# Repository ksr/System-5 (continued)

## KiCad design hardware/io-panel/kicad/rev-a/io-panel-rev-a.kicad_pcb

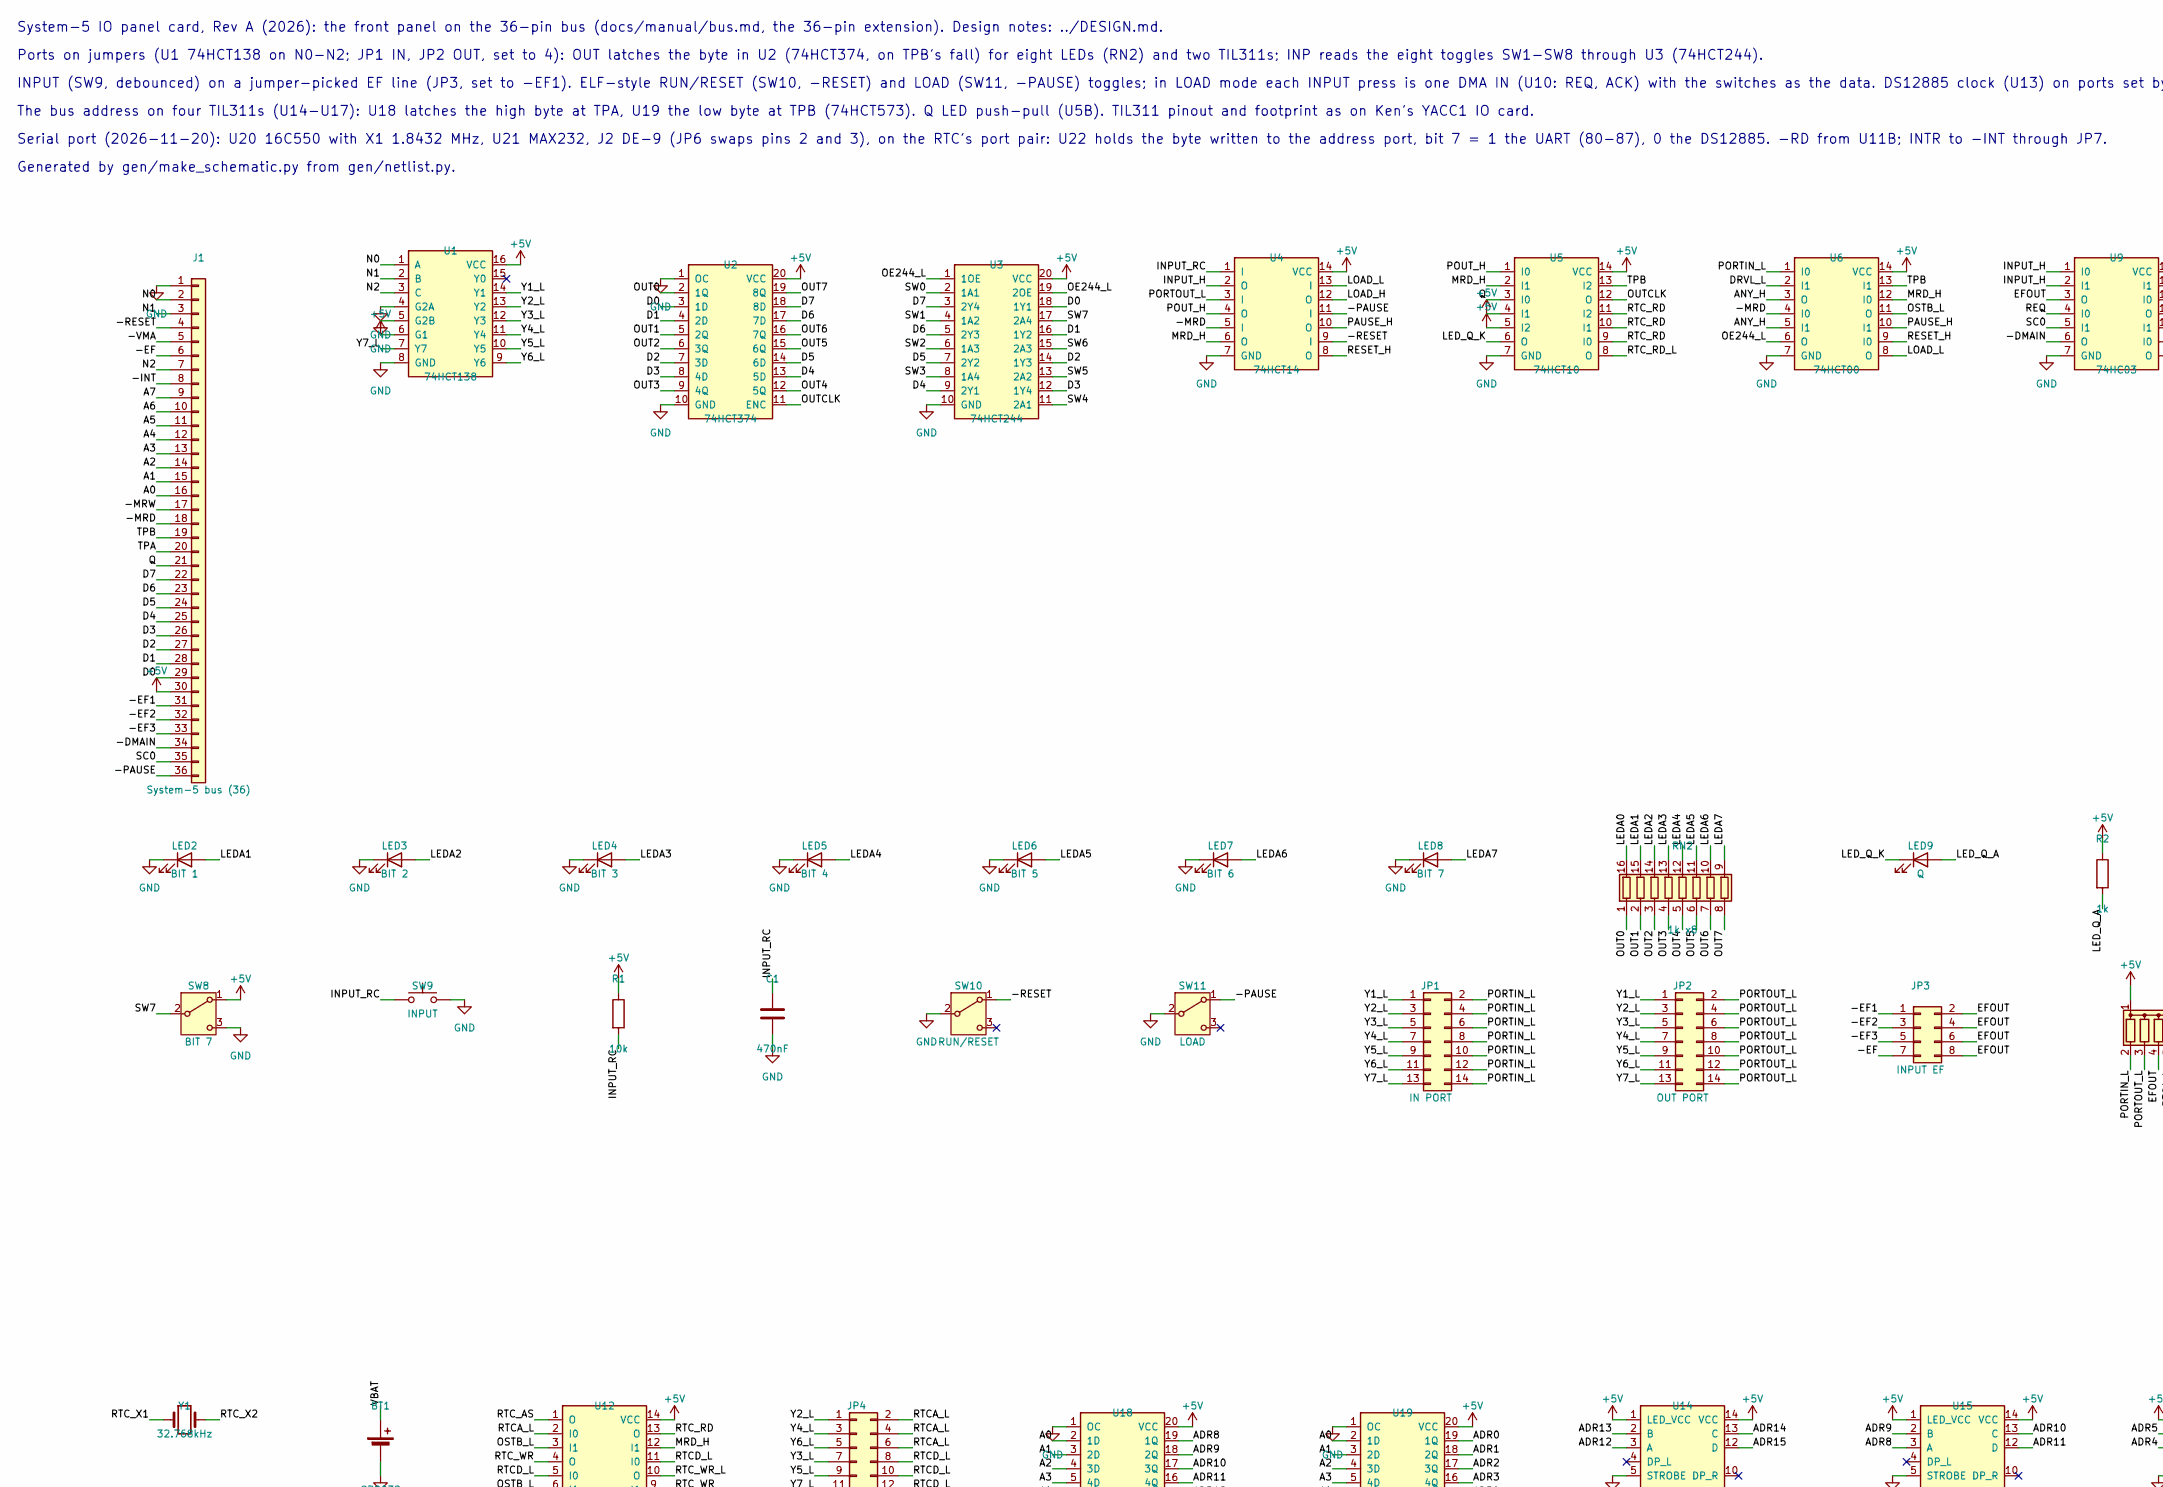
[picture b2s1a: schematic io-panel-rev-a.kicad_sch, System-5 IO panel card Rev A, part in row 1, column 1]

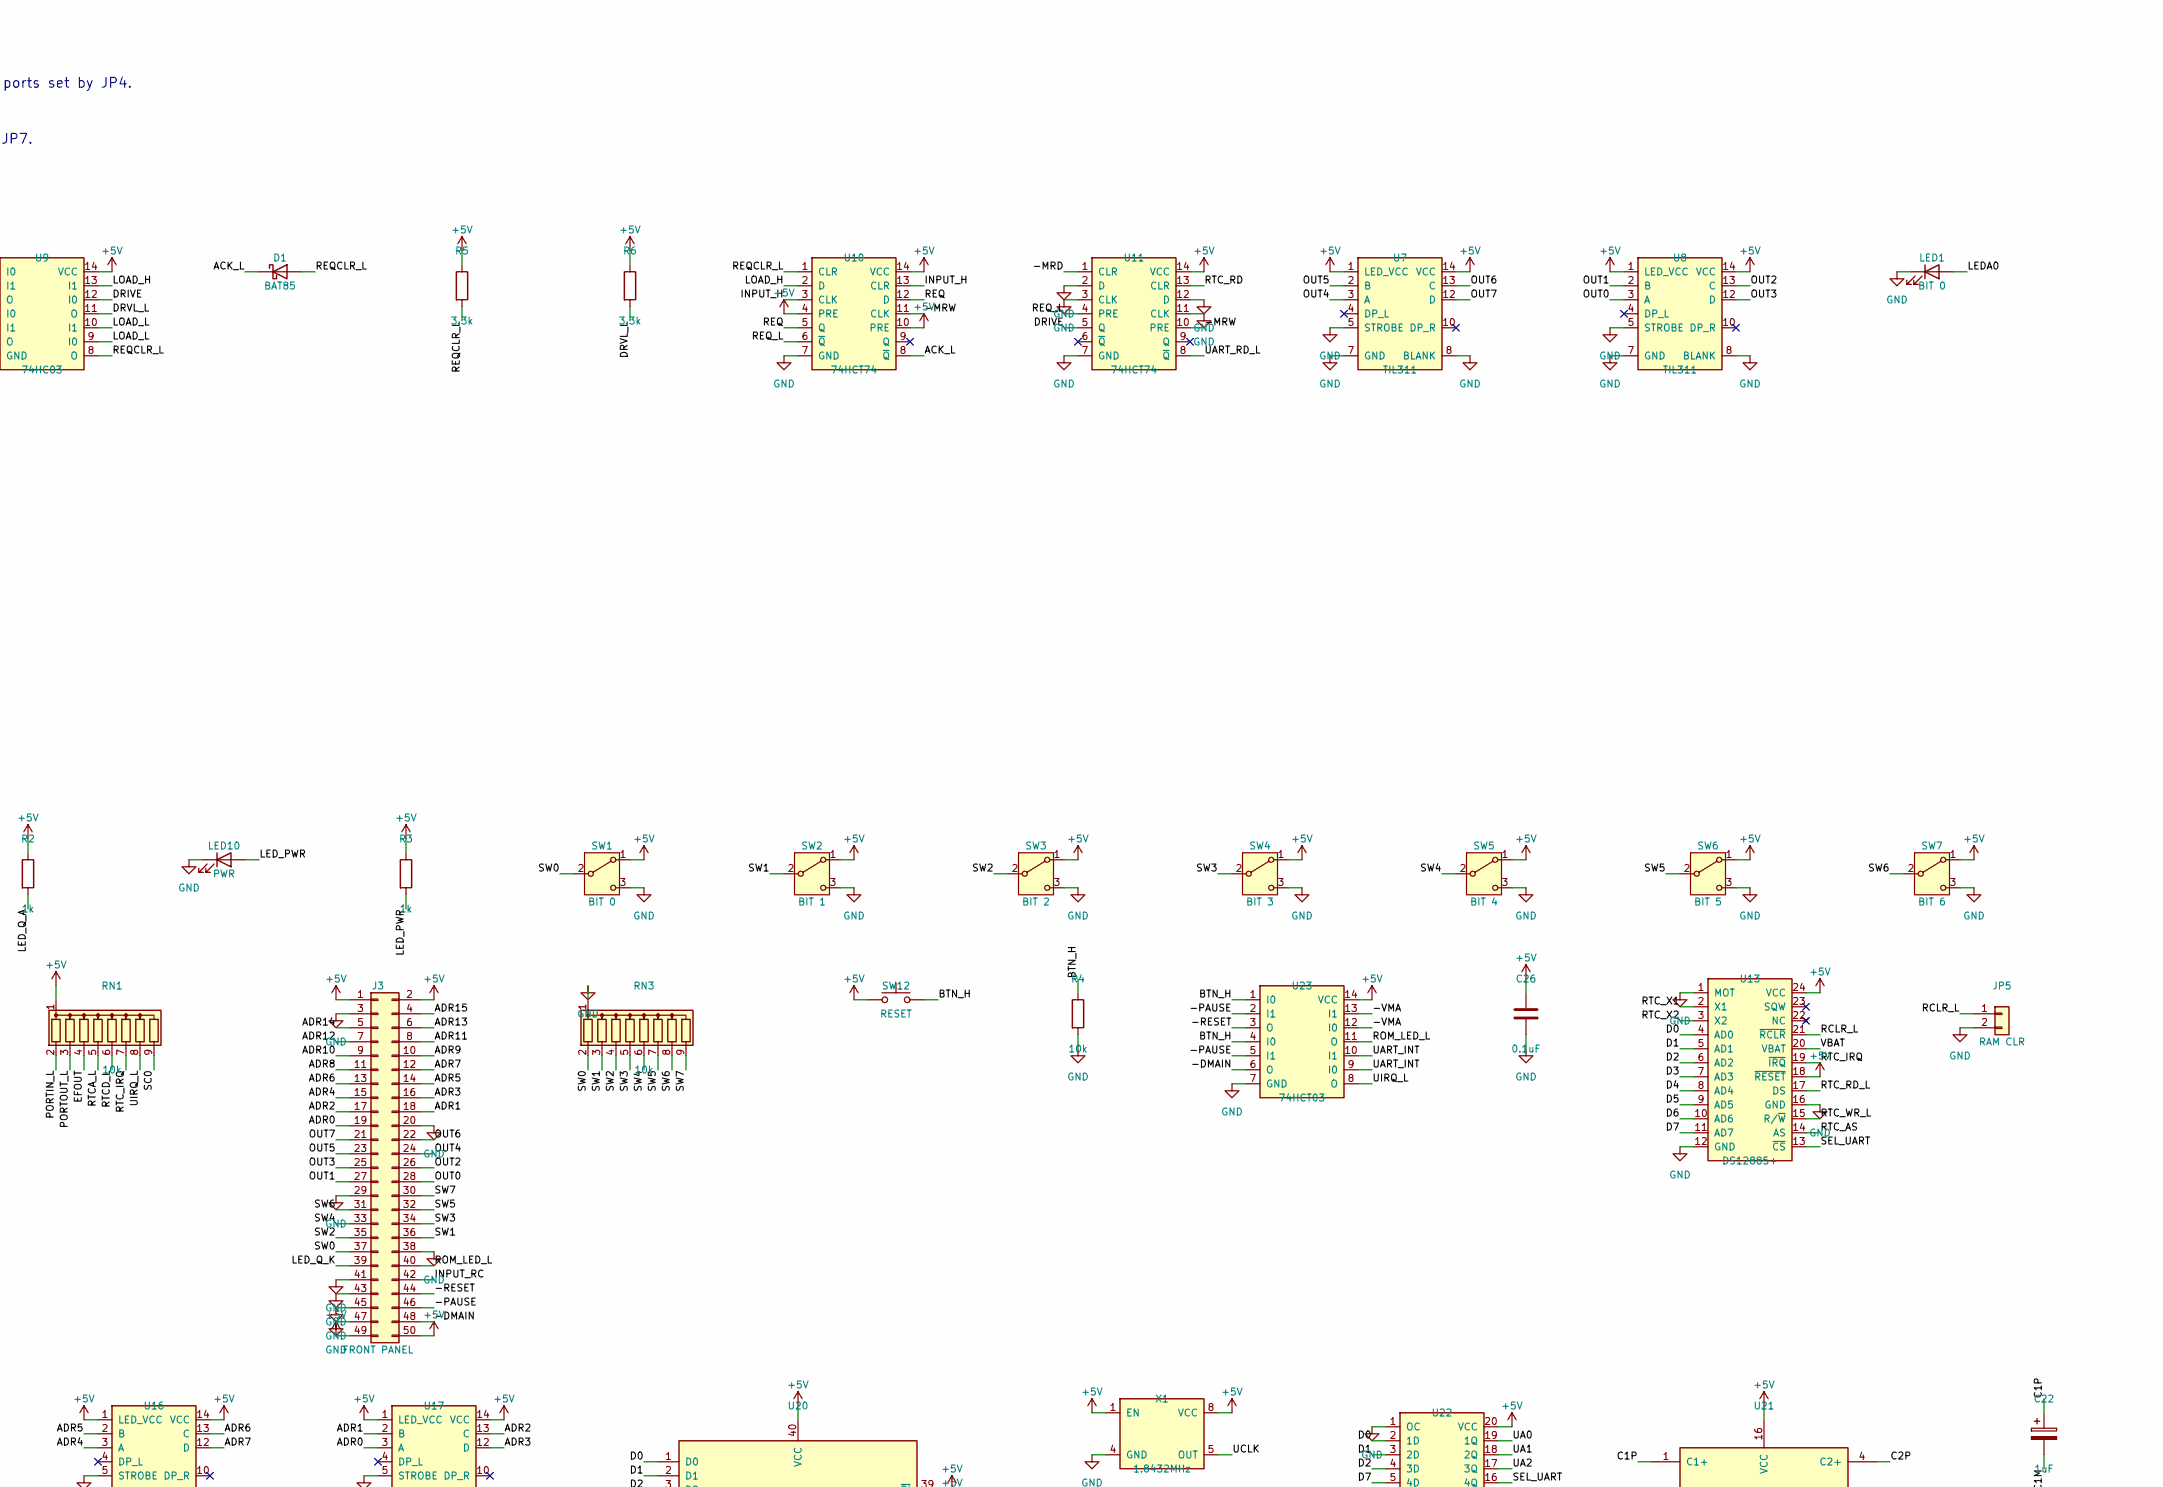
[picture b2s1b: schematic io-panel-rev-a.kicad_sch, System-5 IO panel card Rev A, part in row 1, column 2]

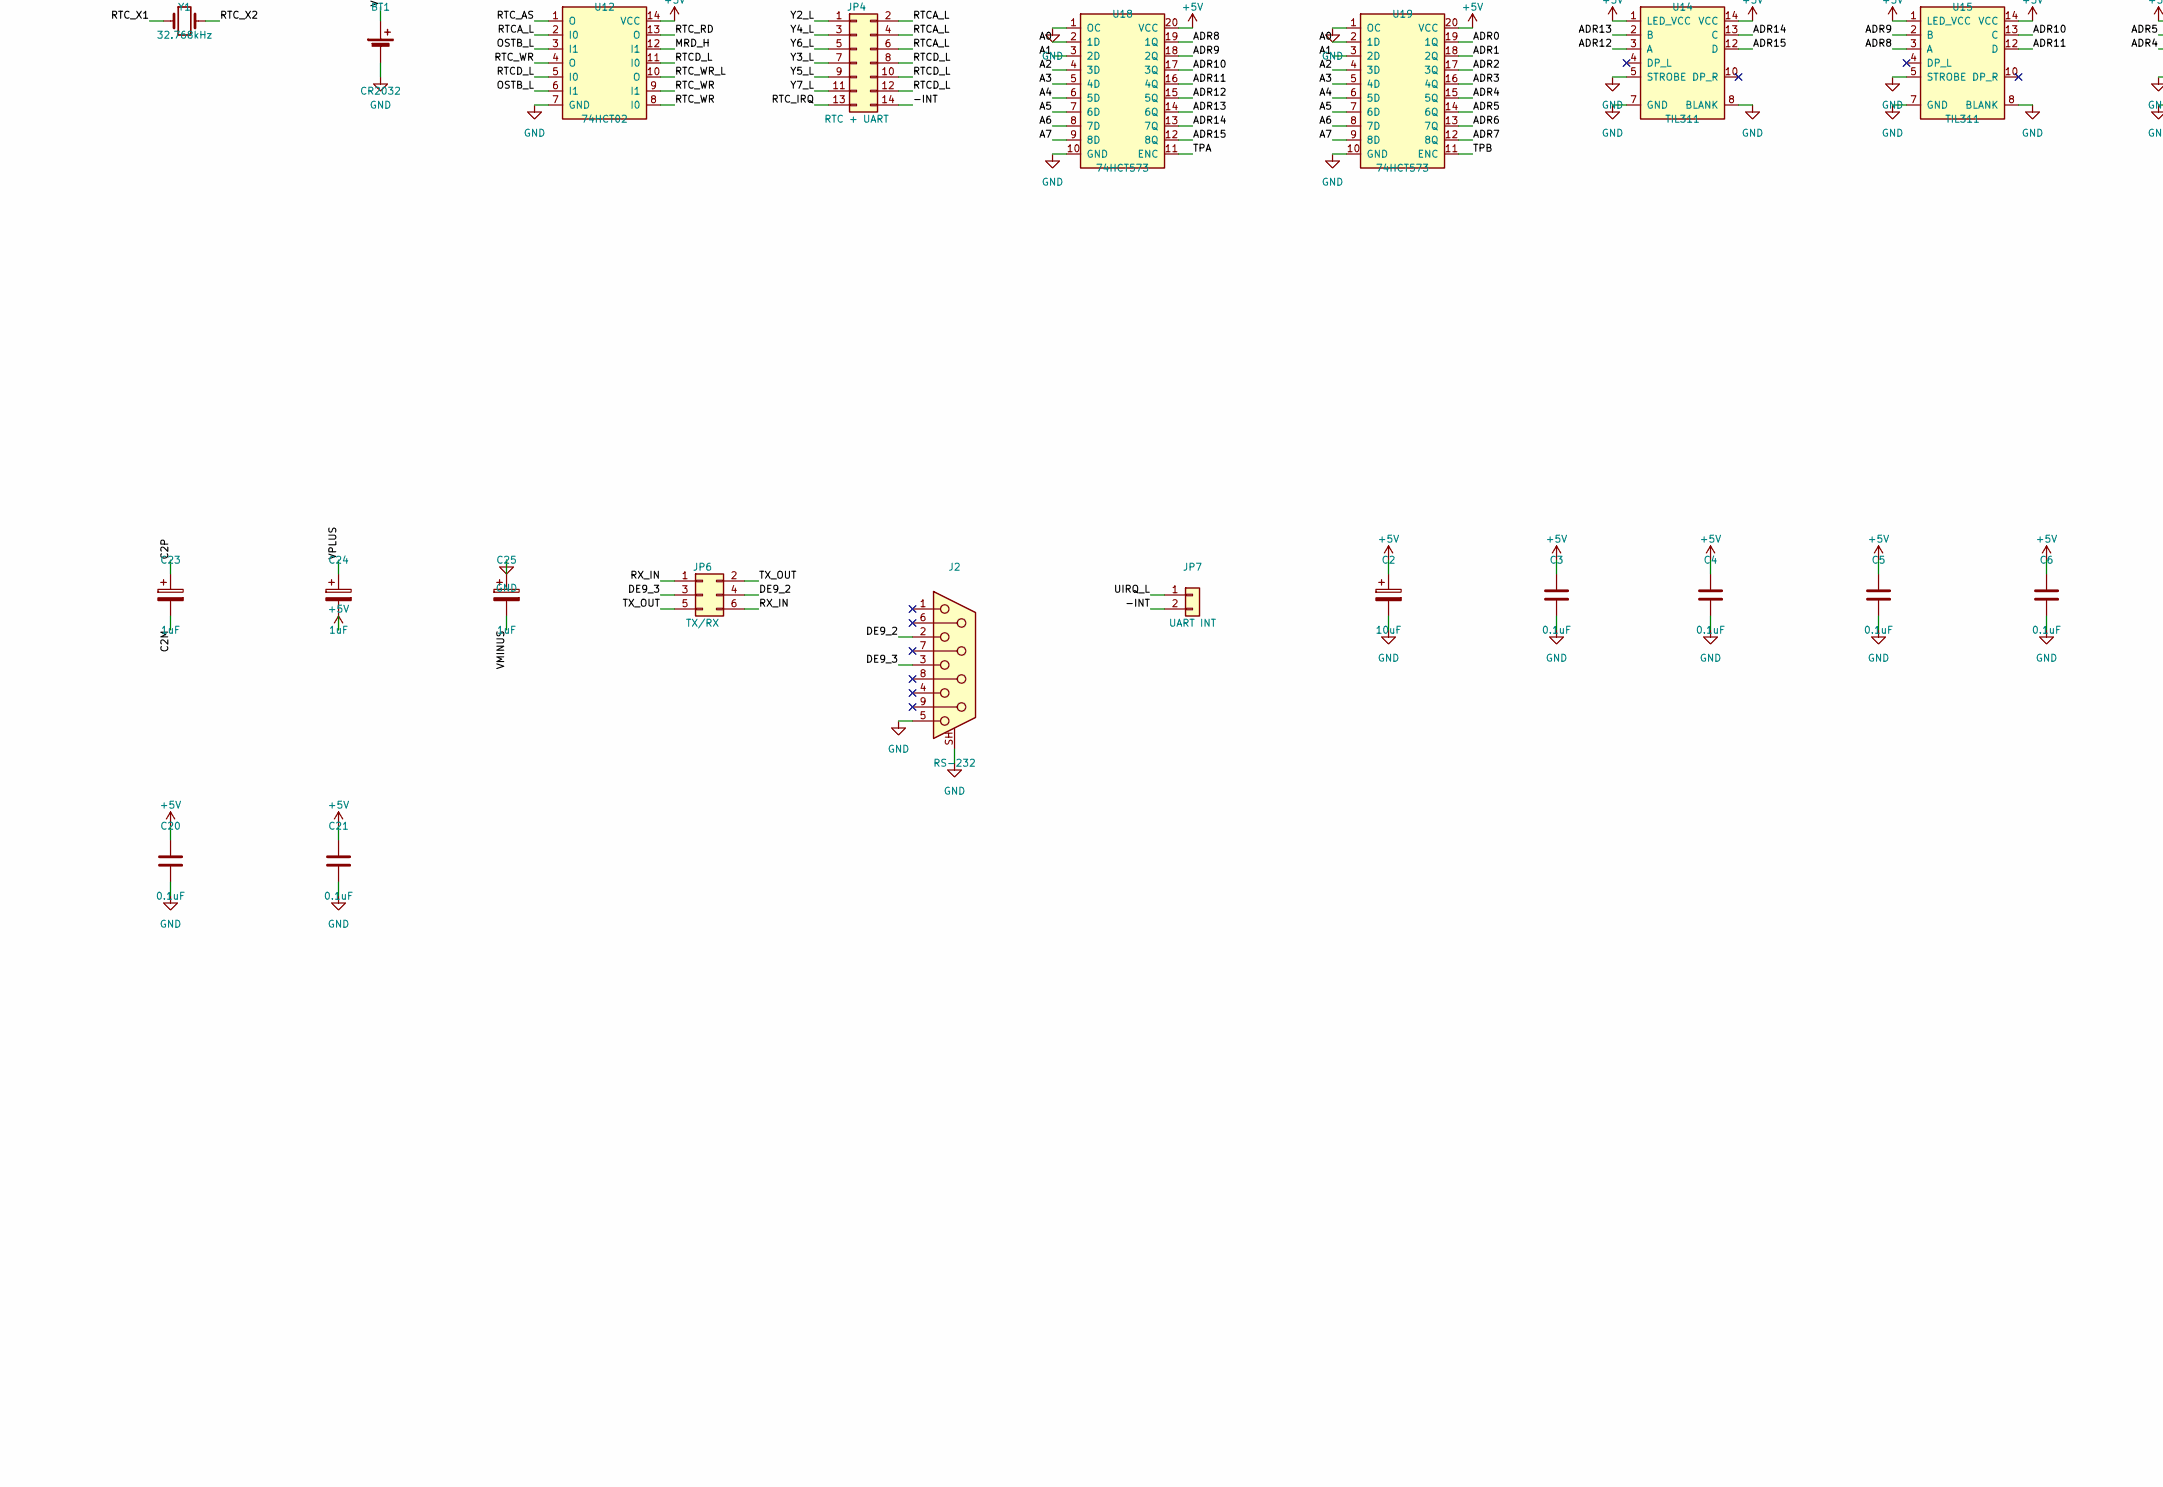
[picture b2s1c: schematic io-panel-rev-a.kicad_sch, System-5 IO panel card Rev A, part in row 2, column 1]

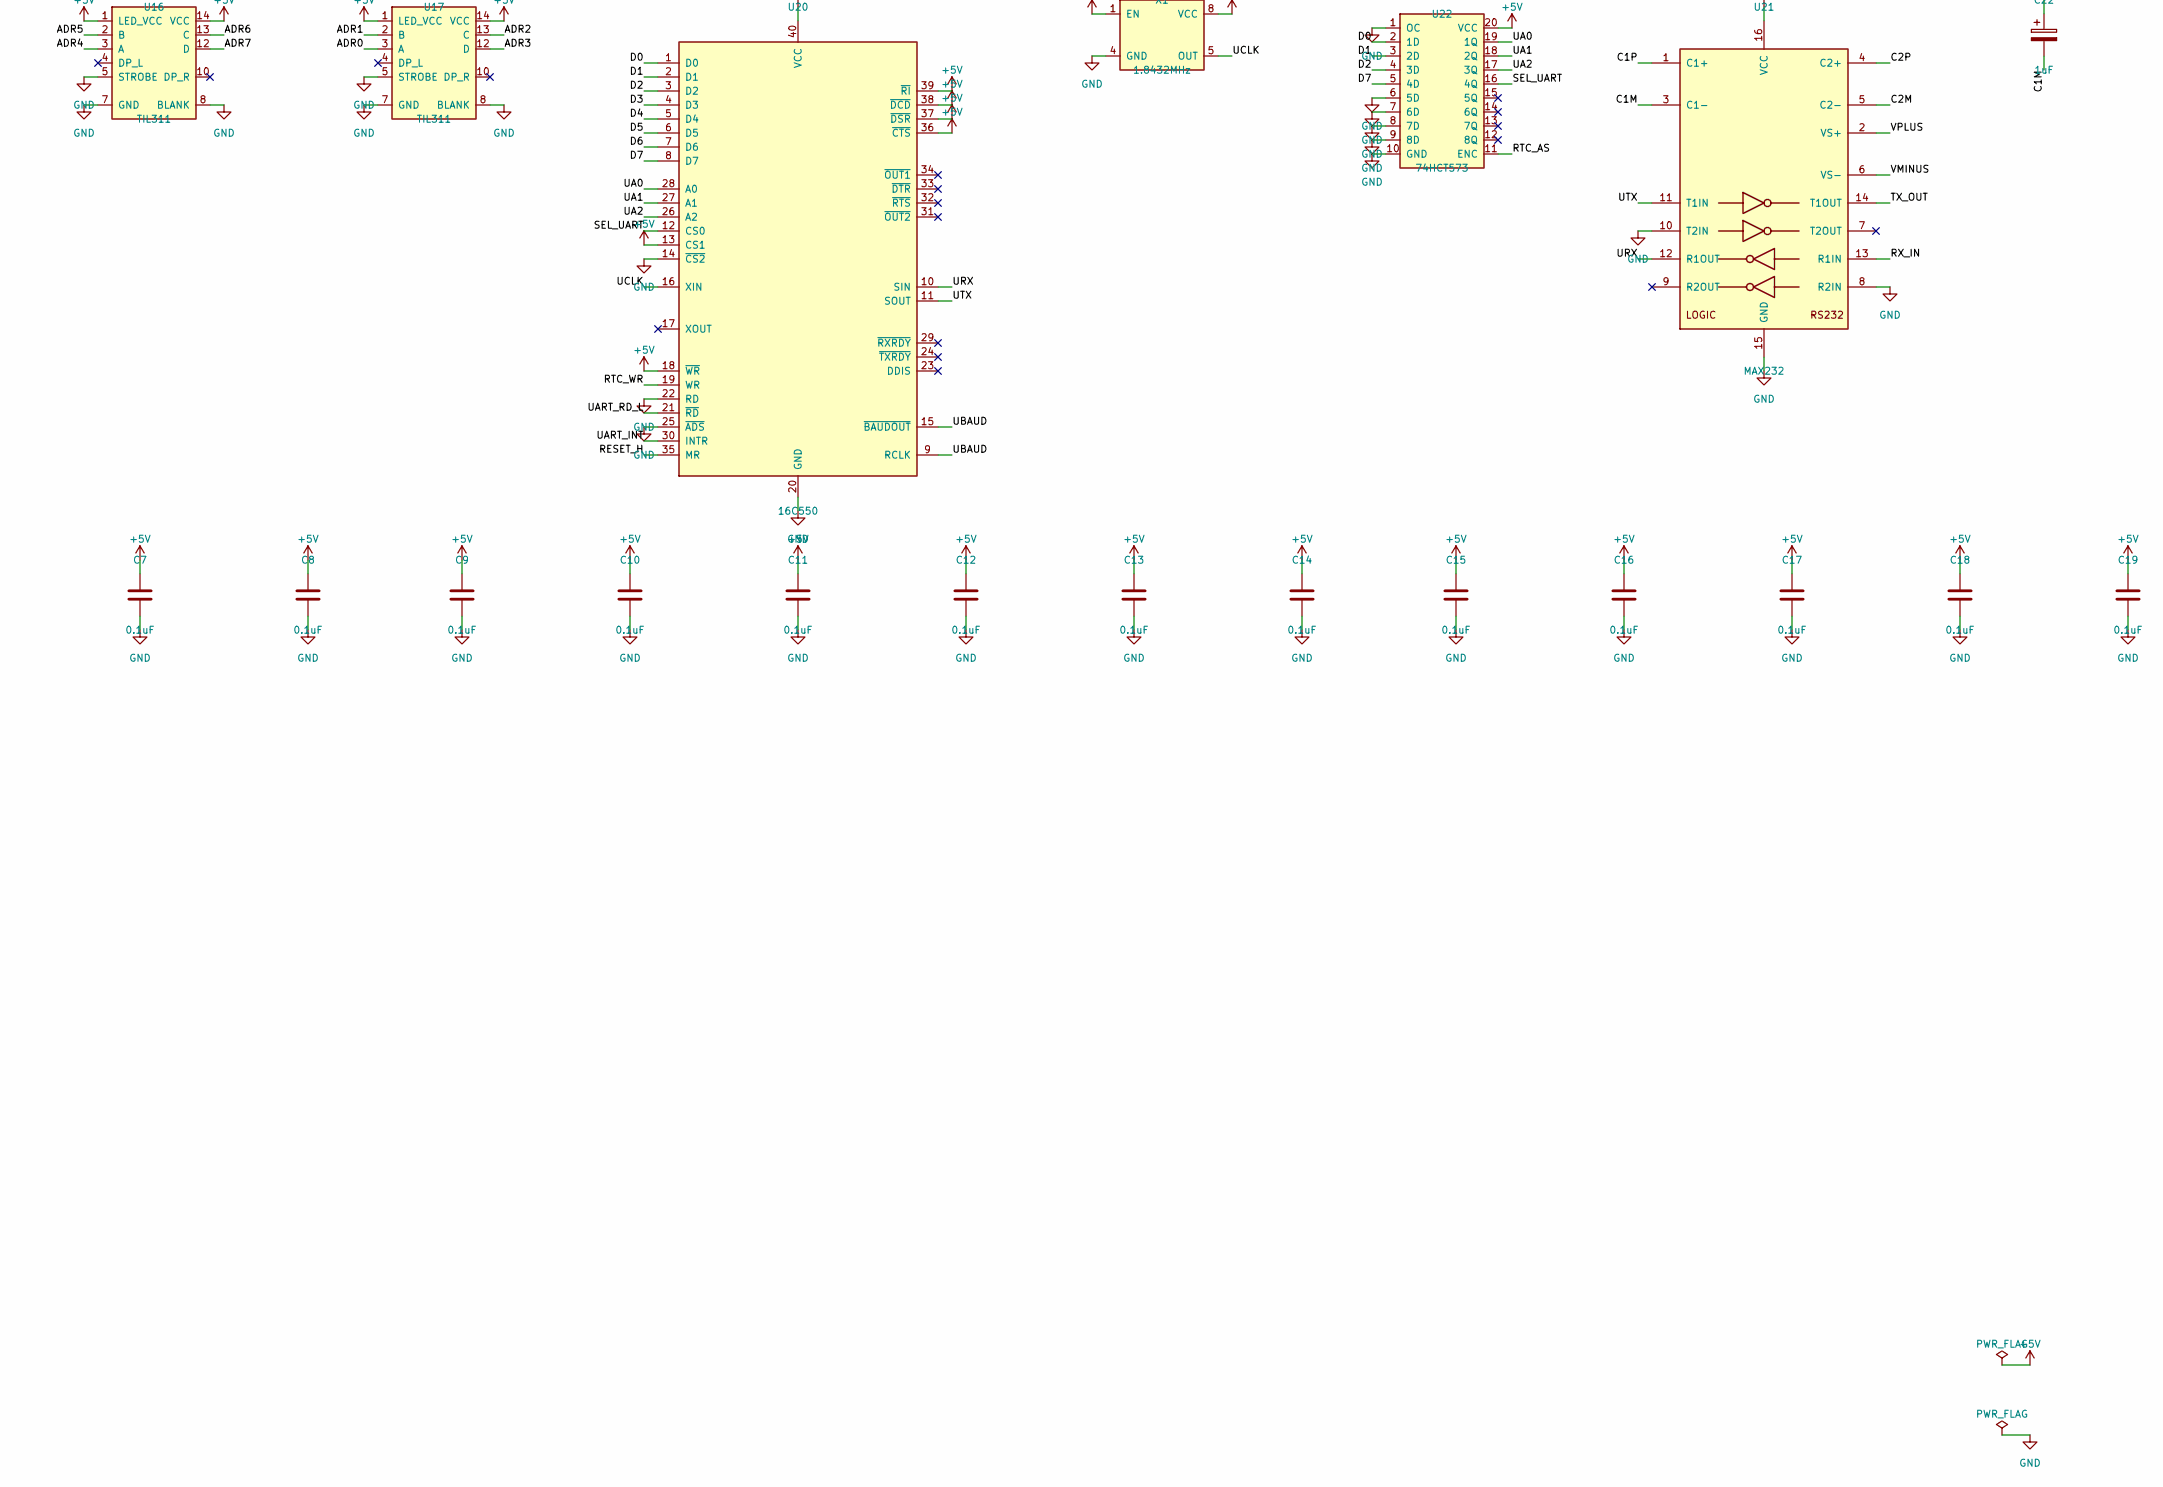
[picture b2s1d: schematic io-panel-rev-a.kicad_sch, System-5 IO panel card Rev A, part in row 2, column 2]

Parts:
BT1: CR2032; BatteryHolder_Keystone_103_1x20mm
C1: 470nF; C_Disc_D5.0mm_W2.5mm_P2.50mm
C2: 10uF; CP_Radial_D5.0mm_P2.00mm
C3, C4, C5, C6, C7, C8, C9, C10, C11, C12, C13, C14, C15, C16, C17, C18, C19, C20, C21, C26: 0.1uF; C025-050X050
C22, C23, C24, C25: 1uF; CP_Radial_D5.0mm_P2.50mm
D1: BAT85; D_DO-35_SOD27_P7.62mm_Horizontal
J1: System-5 bus (36); C36
J2: RS-232; DSUB-9_Socket_Horizontal_P2.77x2.84mm_EdgePinOffset7.70mm_H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
J3: FRONT PANEL; IDC-Header_2x25_P2.54mm_Vertical
JP1: IN PORT; PinHeader_2x07_P2.54mm_Vertical
JP2: OUT PORT; PinHeader_2x07_P2.54mm_Vertical
JP3: INPUT EF; PinHeader_2x04_P2.54mm_Vertical
JP4: RTC + UART; PinHeader_2x07_P2.54mm_Vertical
JP5: RAM CLR; PinHeader_1x02_P2.54mm_Vertical
JP6: TX/RX; PinHeader_2x03_P2.54mm_Vertical
JP7: UART INT; PinHeader_1x02_P2.54mm_Vertical
LED1: BIT 0; LED_D3.0mm
LED2: BIT 1; LED_D3.0mm
LED3: BIT 2; LED_D3.0mm
LED4: BIT 3; LED_D3.0mm
LED5: BIT 4; LED_D3.0mm
LED6: BIT 5; LED_D3.0mm
LED7: BIT 6; LED_D3.0mm
LED8: BIT 7; LED_D3.0mm
LED9: Q; LED_D3.0mm
LED10: PWR; LED_D3.0mm
R1, R4: 10k; R_Axial_DIN0207_L6.3mm_D2.5mm_P7.62mm_Horizontal
R2, R3: 1k; R_Axial_DIN0207_L6.3mm_D2.5mm_P7.62mm_Horizontal
R5, R6: 3.3k; R_Axial_DIN0207_L6.3mm_D2.5mm_P7.62mm_Horizontal
RN1, RN3: 10k; R_Array_SIP9
RN2: 1k x8; DIP-16_W7.62mm
SW1: BIT 0; M9040P
SW2: BIT 1; M9040P
SW3: BIT 2; M9040P
SW4: BIT 3; M9040P
SW5: BIT 4; M9040P
SW6: BIT 5; M9040P
SW7: BIT 6; M9040P
SW8: BIT 7; M9040P
SW9: INPUT; SW_PUSH_6mm
SW10: RUN/RESET; M9040P
SW11: LOAD; M9040P
SW12: RESET; SW_PUSH_6mm
U1: 74HCT138; DIP-16_W7.62mm
U2: 74HCT374; DIP-20_W7.62mm
U3: 74HCT244; DIP-20_W7.62mm
U4: 74HCT14; DIP-14_W7.62mm
U5: 74HCT10; DIP-14_W7.62mm
U6: 74HCT00; DIP-14_W7.62mm
U7, U8, U14, U15, U16, U17: TIL311; HTIL311A
U9: 74HC03; DIP-14_W7.62mm
U10, U11: 74HCT74; DIP-14_W7.62mm
U12: 74HCT02; DIP-14_W7.62mm
U13: DS12885+; DIP-24_W15.24mm
U18, U19, U22: 74HCT573; DIP-20_W7.62mm
U20: 16C550; DIP-40_W15.24mm
U21: MAX232; DIP-16_W7.62mm
U23: 74HCT03; DIP-14_W7.62mm
X1: 1.8432MHz; Oscillator_DIP-8
Y1: 32.768kHz; Crystal_C26-LF_D2.1mm_L6.5mm_Vertical

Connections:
+5V: C2.1, C3.1, C4.1, C5.1, C6.1, C7.1, C8.1, C9.1, C10.1, C11.1, C12.1, C13.1, C14.1, C15.1, C16.1, C17.1, C18.1, C19.1, C20.1, C21.1, C24.2, C26.1, J1.30, J3.1, J3.2, J3.49, J3.50, R1.1, R2.1, R3.1, R5.1, R6.1, RN1.1 (common), SW1.1 (A), SW2.1 (A), SW3.1 (A), SW4.1 (A), SW5.1 (A), SW6.1 (A), SW7.1 (A), SW8.1 (A), SW12.1, U1.6 (G1), U1.16 (VCC), U2.20 (VCC), U3.20 (VCC), U4.14 (VCC), U5.4 (I1), U5.5 (I2), U5.14 (VCC), U6.14 (VCC), U7.1 (LED_VCC), U7.14 (VCC), U8.1 (LED_VCC), U8.14 (VCC), U9.14 (VCC), U10.4 (PRE), U10.10 (PRE), U10.14 (VCC), U11.14 (VCC), U12.14 (VCC), U13.18 (~RESET), U13.24 (VCC), U14.1 (LED_VCC), U14.14 (VCC), U15.1 (LED_VCC), U15.14 (VCC), U16.1 (LED_VCC), U16.14 (VCC), U17.1 (LED_VCC), U17.14 (VCC), U18.20 (VCC), U19.20 (VCC), U20.13 (CS1), U20.18 (~WR), U20.36 (~CTS), U20.37 (~DSR), U20.38 (~DCD), U20.39 (~RI), U20.40 (VCC), U21.16 (VCC), U22.20 (VCC), U23.14 (VCC), X1.1 (EN), X1.8 (VCC)
/-DMAIN: J1.34, J3.48, U9.6 (O), U23.6 (O)
/-EF: J1.6, JP3.7
/-EF1: J1.31, JP3.1
/-EF2: J1.32, JP3.3
/-EF3: J1.33, JP3.5
/-INT: J1.8, JP4.14, JP7.2
/-MRD: J1.18, U4.5 (I), U6.4 (I0), U11.1 (CLR)
/-MRW: J1.17, U10.11 (CLK), U11.10 (PRE)
/-PAUSE: J1.36, J3.46, SW11.1 (A), U4.11 (I), U23.2 (I1), U23.5 (I1)
/-RESET: J1.4, J3.44, SW10.1 (A), U4.9 (I), U23.3 (O)
/-VMA: J1.5, U23.12 (I0), U23.13 (I1)
/A0: J1.16, U18.2 (1D), U19.2 (1D)
/A1: J1.15, U18.3 (2D), U19.3 (2D)
/A2: J1.14, U18.4 (3D), U19.4 (3D)
/A3: J1.13, U18.5 (4D), U19.5 (4D)
/A4: J1.12, U18.6 (5D), U19.6 (5D)
/A5: J1.11, U18.7 (6D), U19.7 (6D)
/A6: J1.10, U18.8 (7D), U19.8 (7D)
/A7: J1.9, U18.9 (8D), U19.9 (8D)
/ACK_L: D1.1 (K), U10.8 (~Q)
/ADR0: J3.19, U17.3 (A), U19.19 (1Q)
/ADR1: J3.18, U17.2 (B), U19.18 (2Q)
/ADR2: J3.17, U17.13 (C), U19.17 (3Q)
/ADR3: J3.16, U17.12 (D), U19.16 (4Q)
/ADR4: J3.15, U16.3 (A), U19.15 (5Q)
/ADR5: J3.14, U16.2 (B), U19.14 (6Q)
/ADR6: J3.13, U16.13 (C), U19.13 (7Q)
/ADR7: J3.12, U16.12 (D), U19.12 (8Q)
/ADR8: J3.11, U15.3 (A), U18.19 (1Q)
/ADR9: J3.10, U15.2 (B), U18.18 (2Q)
/ADR10: J3.9, U15.13 (C), U18.17 (3Q)
/ADR11: J3.8, U15.12 (D), U18.16 (4Q)
/ADR12: J3.7, U14.3 (A), U18.15 (5Q)
/ADR13: J3.6, U14.2 (B), U18.14 (6Q)
/ADR14: J3.5, U14.13 (C), U18.13 (7Q)
/ADR15: J3.4, U14.12 (D), U18.12 (8Q)
/ANY_H: U6.3 (O), U6.5 (I1)
/BTN_H: R4.1, SW12.2, U23.1 (I0), U23.4 (I0)
/C1M: C22.2, U21.3 (C1-)
/C1P: C22.1, U21.1 (C1+)
/C2M: C23.2, U21.5 (C2-)
/C2P: C23.1, U21.4 (C2+)
/D0: J1.29, U2.3 (1D), U3.18 (1Y1), U13.4 (AD0), U20.1 (D0), U22.2 (1D)
/D1: J1.28, U2.4 (2D), U3.16 (1Y2), U13.5 (AD1), U20.2 (D1), U22.3 (2D)
/D2: J1.27, U2.7 (3D), U3.14 (1Y3), U13.6 (AD2), U20.3 (D2), U22.4 (3D)
/D3: J1.26, U2.8 (4D), U3.12 (1Y4), U13.7 (AD3), U20.4 (D3)
/D4: J1.25, U2.13 (5D), U3.9 (2Y1), U13.8 (AD4), U20.5 (D4)
/D5: J1.24, U2.14 (6D), U3.7 (2Y2), U13.9 (AD5), U20.6 (D5)
/D6: J1.23, U2.17 (7D), U3.5 (2Y3), U13.10 (AD6), U20.7 (D6)
/D7: J1.22, U2.18 (8D), U3.3 (2Y4), U13.11 (AD7), U20.8 (D7), U22.5 (4D)
/DE9_2: J2.2, JP6.4
/DE9_3: J2.3, JP6.3
/DRIVE: U9.12 (I0), U11.5 (Q)
/DRVL_L: R6.2, U6.2 (I1), U9.11 (O)
/EFOUT: JP3.2, JP3.4, JP3.6, JP3.8, RN1.4 (R3), U9.3 (O)
/INPUT_H: U4.2 (O), U9.1 (I0), U9.2 (I1), U10.3 (CLK), U10.13 (CLR)
/INPUT_RC: C1.1, J3.42, R1.2, SW9.1, U4.1 (I)
/LEDA0: LED1.2 (A), RN2.16 (R1.2)
/LEDA1: LED2.2 (A), RN2.15 (R2.2)
/LEDA2: LED3.2 (A), RN2.14 (R3.2)
/LEDA3: LED4.2 (A), RN2.13 (R4.2)
/LEDA4: LED5.2 (A), RN2.12 (R5.2)
/LEDA5: LED6.2 (A), RN2.11 (R6.2)
/LEDA6: LED7.2 (A), RN2.10 (R7.2)
/LEDA7: LED8.2 (A), RN2.9 (R8.2)
/LED_PWR: LED10.2 (A), R3.2
/LED_Q_A: LED9.2 (A), R2.2
/LED_Q_K: J3.39, LED9.1 (K), U5.6 (O)
/LOAD_H: U4.12 (O), U9.13 (I1), U10.2 (D)
/LOAD_L: U4.13 (I), U6.8 (O), U9.9 (I0), U9.10 (I1)
/MRD_H: U4.6 (O), U5.2 (I1), U6.12 (I0), U12.12 (I1)
/N0: J1.2, U1.1 (A)
/N1: J1.3, U1.2 (B)
/N2: J1.7, U1.3 (C)
/OE244_L: U3.1 (1OE), U3.19 (2OE), U6.6 (O)
/OSTB_L: U6.11 (O), U12.3 (I1), U12.6 (I1)
/OUT0: J3.28, RN2.1 (R1.1), U2.2 (1Q), U8.3 (A)
/OUT1: J3.27, RN2.2 (R2.1), U2.5 (2Q), U8.2 (B)
/OUT2: J3.26, RN2.3 (R3.1), U2.6 (3Q), U8.13 (C)
/OUT3: J3.25, RN2.4 (R4.1), U2.9 (4Q), U8.12 (D)
/OUT4: J3.24, RN2.5 (R5.1), U2.12 (5Q), U7.3 (A)
/OUT5: J3.23, RN2.6 (R6.1), U2.15 (6Q), U7.2 (B)
/OUT6: J3.22, RN2.7 (R7.1), U2.16 (7Q), U7.13 (C)
/OUT7: J3.21, RN2.8 (R8.1), U2.19 (8Q), U7.12 (D)
/OUTCLK: U2.11 (ENC), U5.12 (O)
/PAUSE_H: U4.10 (O), U6.10 (I1)
/PORTIN_L: JP1.2, JP1.4, JP1.6, JP1.8, JP1.10, JP1.12, JP1.14, RN1.2 (R1), U6.1 (I0)
/PORTOUT_L: JP2.2, JP2.4, JP2.6, JP2.8, JP2.10, JP2.12, JP2.14, RN1.3 (R2), U4.3 (I)
/POUT_H: U4.4 (O), U5.1 (I0)
/Q: J1.21, U5.3 (I0)
/RCLR_L: JP5.1, U13.21 (~RCLR)
/REQ: U9.4 (I0), U10.5 (Q), U10.12 (D)
/REQCLR_L: D1.2 (A), R5.2, U9.8 (O), U10.1 (CLR)
/REQ_L: U10.6 (~Q), U11.4 (PRE)
/RESET_H: U4.8 (O), U6.9 (I0), U20.35 (MR)
/ROM_LED_L: J3.40, U23.11 (O)
/RTCA_L: JP4.2, JP4.4, JP4.6, RN1.5 (R4), U12.2 (I0)
/RTCD_L: JP4.8, JP4.10, JP4.12, RN1.6 (R5), U12.5 (I0), U12.11 (I0)
/RTC_AS: U12.1 (O), U13.14 (AS), U22.11 (ENC)
/RTC_IRQ: JP4.13, RN1.7 (R6), U13.19 (~IRQ)
/RTC_RD: U5.9 (I0), U5.10 (I1), U5.11 (I2), U11.13 (CLR), U12.13 (O)
/RTC_RD_L: U5.8 (O), U13.17 (DS)
/RTC_WR: U12.4 (O), U12.8 (I0), U12.9 (I1), U20.19 (WR)
/RTC_WR_L: U12.10 (O), U13.15 (R/~W)
/RTC_X1: U13.2 (X1), Y1.1
/RTC_X2: U13.3 (X2), Y1.2
/RX_IN: JP6.1, JP6.6, U21.13 (R1IN)
/SC0: J1.35, RN1.9 (R8), U9.5 (I1)
/SEL_UART: U13.13 (~CS), U20.12 (CS0), U22.16 (4Q)
/SW0: J3.37, RN3.2 (R1), SW1.2 (B), U3.2 (1A1)
/SW1: J3.36, RN3.3 (R2), SW2.2 (B), U3.4 (1A2)
/SW2: J3.35, RN3.4 (R3), SW3.2 (B), U3.6 (1A3)
/SW3: J3.34, RN3.5 (R4), SW4.2 (B), U3.8 (1A4)
/SW4: J3.33, RN3.6 (R5), SW5.2 (B), U3.11 (2A1)
/SW5: J3.32, RN3.7 (R6), SW6.2 (B), U3.13 (2A2)
/SW6: J3.31, RN3.8 (R7), SW7.2 (B), U3.15 (2A3)
/SW7: J3.30, RN3.9 (R8), SW8.2 (B), U3.17 (2A4)
/TPA: J1.20, U18.11 (ENC)
/TPB: J1.19, U5.13 (I2), U6.13 (I1), U19.11 (ENC)
/TX_OUT: JP6.2, JP6.5, U21.14 (T1OUT)
/UA0: U20.28 (A0), U22.19 (1Q)
/UA1: U20.27 (A1), U22.18 (2Q)
/UA2: U20.26 (A2), U22.17 (3Q)
/UART_INT: U20.30 (INTR), U23.9 (I0), U23.10 (I1)
/UART_RD_L: U11.8 (~Q), U20.21 (~RD)
/UBAUD: U20.9 (RCLK), U20.15 (~BAUDOUT)
/UCLK: U20.16 (XIN), X1.5 (OUT)
/UIRQ_L: JP7.1, RN1.8 (R7), U23.8 (O)
/URX: U20.10 (SIN), U21.12 (R1OUT)
/UTX: U20.11 (SOUT), U21.11 (T1IN)
/VBAT: BT1.1 (+), U13.20 (VBAT)
/VMINUS: C25.2, U21.6 (VS-)
/VPLUS: C24.1, U21.2 (VS+)
/Y1_L: JP1.1, JP2.1, U1.14 (Y1)
/Y2_L: JP1.3, JP2.3, JP4.1, U1.13 (Y2)
/Y3_L: JP1.5, JP2.5, JP4.7, U1.12 (Y3)
/Y4_L: JP1.7, JP2.7, JP4.3, U1.11 (Y4)
/Y5_L: JP1.9, JP2.9, JP4.9, U1.10 (Y5)
/Y6_L: JP1.11, JP2.11, JP4.5, U1.9 (Y6)
/Y7_L: JP1.13, JP2.13, JP4.11, U1.7 (Y7)
GND: BT1.2 (-), C1.2, C2.2, C3.2, C4.2, C5.2, C6.2, C7.2, C8.2, C9.2, C10.2, C11.2, C12.2, C13.2, C14.2, C15.2, C16.2, C17.2, C18.2, C19.2, C20.2, C21.2, C25.1, C26.2, J1.1, J2.5, J2.SH (PAD), J3.3, J3.20, J3.29, J3.38, J3.41, J3.43, J3.45, J3.47, JP5.2, LED1.1 (K), LED2.1 (K), LED3.1 (K), LED4.1 (K), LED5.1 (K), LED6.1 (K), LED7.1 (K), LED8.1 (K), LED10.1 (K), R4.2, RN3.1 (common), SW1.3 (C), SW2.3 (C), SW3.3 (C), SW4.3 (C), SW5.3 (C), SW6.3 (C), SW7.3 (C), SW8.3 (C), SW9.2, SW10.2 (B), SW11.2 (B), U1.4 (G2A), U1.5 (G2B), U1.8 (GND), U2.1 (OC), U2.10 (GND), U3.10 (GND), U4.7 (GND), U5.7 (GND), U6.7 (GND), U7.5 (STROBE), U7.7 (GND), U7.8 (BLANK), U8.5 (STROBE), U8.7 (GND), U8.8 (BLANK), U9.7 (GND), U10.7 (GND), U11.2 (D), U11.3 (CLK), U11.7 (GND), U11.11 (CLK), U11.12 (D), U12.7 (GND), U13.1 (MOT), U13.12 (GND), U13.16 (GND), U14.5 (STROBE), U14.7 (GND), U14.8 (BLANK), U15.5 (STROBE), U15.7 (GND), U15.8 (BLANK), U16.5 (STROBE), U16.7 (GND), U16.8 (BLANK), U17.5 (STROBE), U17.7 (GND), U17.8 (BLANK), U18.1 (OC), U18.10 (GND), U19.1 (OC), U19.10 (GND), U20.14 (~CS2), U20.20 (GND), U20.22 (RD), U20.25 (~ADS), U21.8 (R2IN), U21.10 (T2IN), U21.15 (GND), U22.1 (OC), U22.6 (5D), U22.7 (6D), U22.8 (7D), U22.9 (8D), U22.10 (GND), U23.7 (GND), X1.4 (GND)

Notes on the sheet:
System-5 IO panel card, Rev A (2026): the front panel on the 36-pin bus (docs/manual/bus.md, the 36-pin extension). Design notes: ../DESIGN.md.
Ports on jumpers (U1 74HCT138 on N0-N2; JP1 IN, JP2 OUT, set to 4): OUT latches the byte in U2 (74HCT374, on TPB's fall) for eight LEDs (RN2) and two TIL311s; INP reads the eight toggles SW1-SW8 through U3 (74HCT244).
INPUT (SW9, debounced) on a jumper-picked EF line (JP3, set to -EF1). ELF-style RUN/RESET (SW10, -RESET) and LOAD (SW11, -PAUSE) toggles; in LOAD mode each INPUT press is one DMA IN (U10: REQ, ACK) with the switches as the data. DS12885 clock (U13) on ports set by JP4.
The bus address on four TIL311s (U14-U17): U18 latches the high byte at TPA, U19 the low byte at TPB (74HCT573). Q LED push-pull (U5B). TIL311 pinout and footprint as on Ken's YACC1 IO card.
Serial port (2026-11-20): U20 16C550 with X1 1.8432 MHz, U21 MAX232, J2 DE-9 (JP6 swaps pins 2 and 3), on the RTC's port pair: U22 holds the byte written to the address port, bit 7 = 1 the UART (80-87), 0 the DS12885. -RD from U11B; INTR to -INT through JP7.
Generated by gen/make_schematic.py from gen/netlist.py.

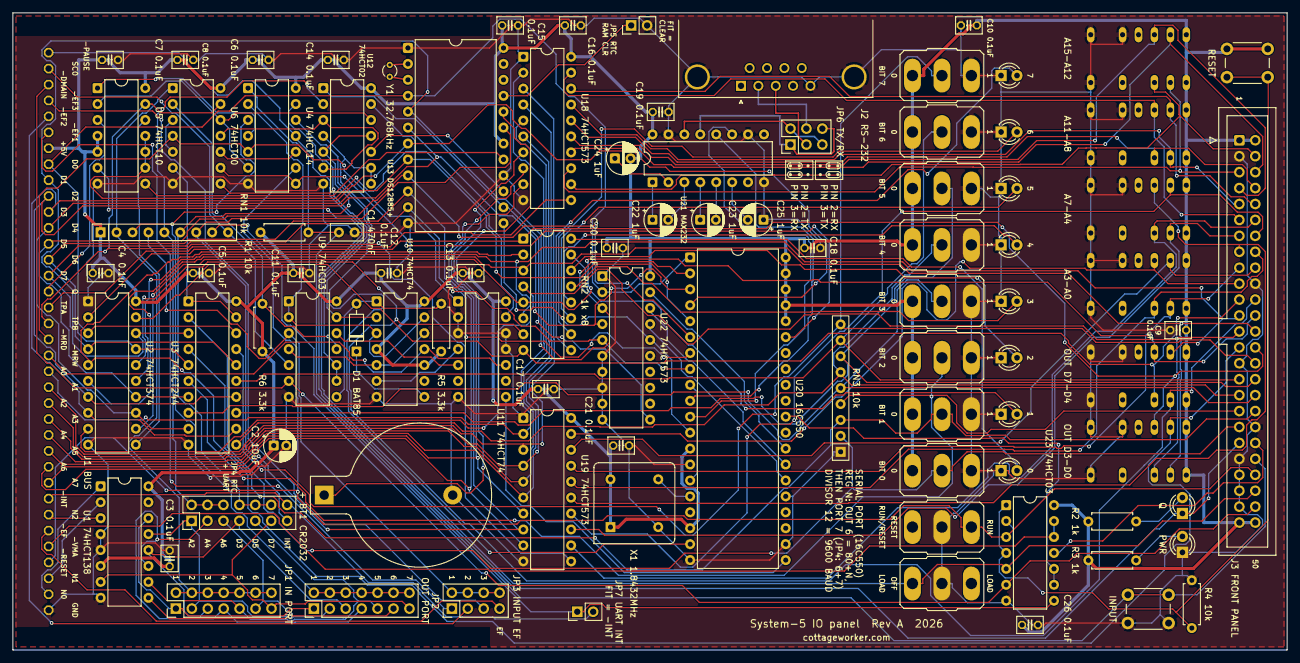
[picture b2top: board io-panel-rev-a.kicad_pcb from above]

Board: 2 copper layers, 203.2 x 101.6 mm, 94 parts (0 on the bottom side), 142 nets.
